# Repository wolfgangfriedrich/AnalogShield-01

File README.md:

# AnalogShield-01
Arduino Schield Pixi Analog I/O 20channel KiCAD design files

Project is hosted at HackADay.io 
https://hackaday.io/project/4397-pixi-analog-shield

Arduino library and sample code are storedin a separate repository 
https://github.com/wolfgangfriedrich/Pixi_demo

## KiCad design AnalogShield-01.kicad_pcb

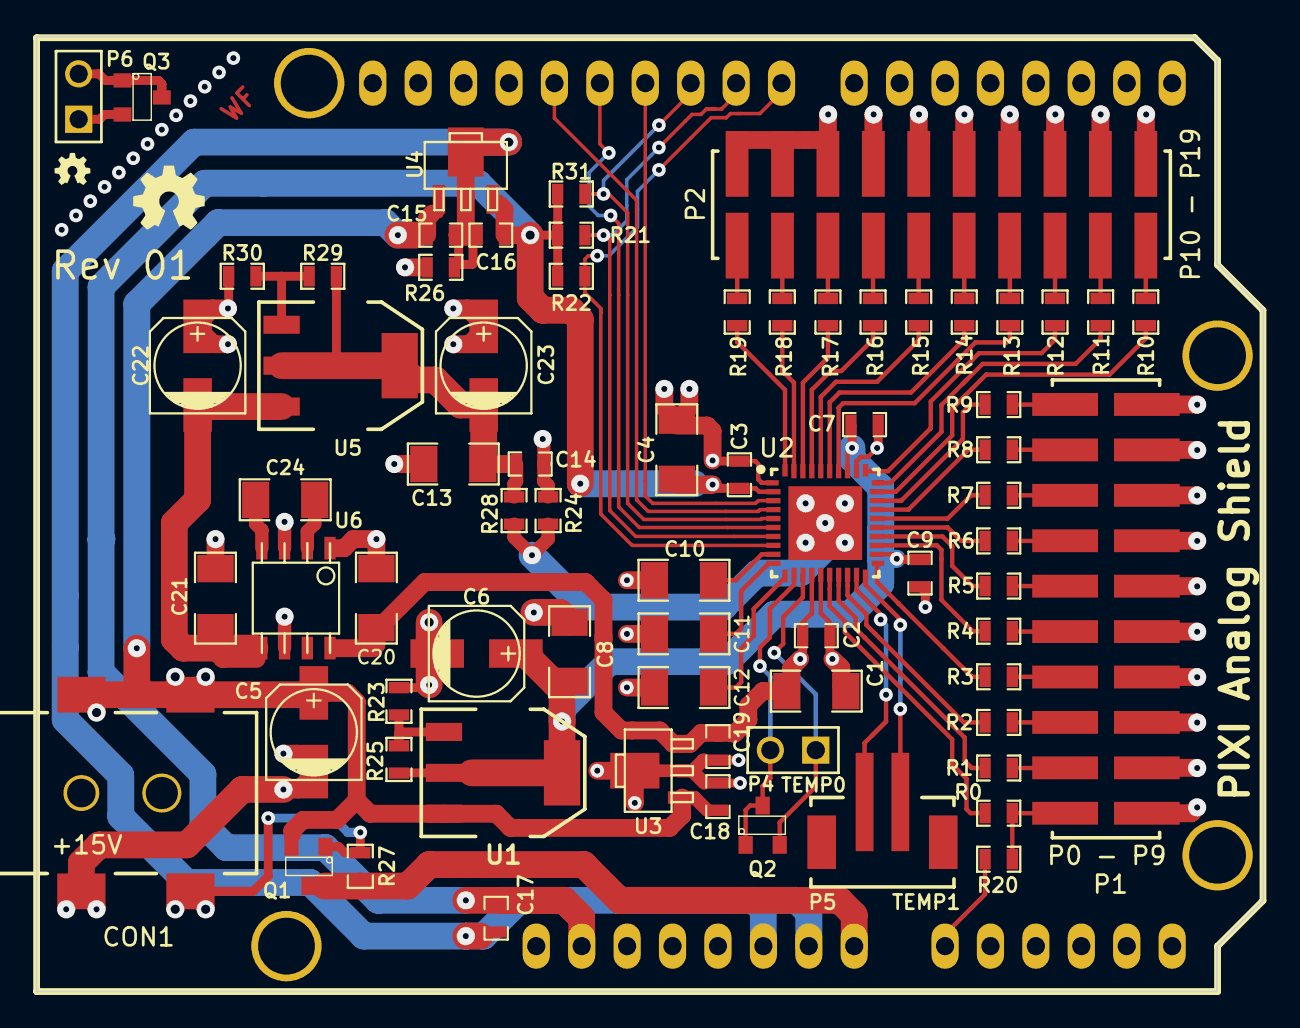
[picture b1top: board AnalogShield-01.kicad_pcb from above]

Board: 2 copper layers, 68.6 x 53.4 mm, 74 parts (0 on the bottom side), 71 nets.

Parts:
C1, C4, C8, C10, C11, C12, C13, C20, C21, C24: 10uF; SM1206
C2, C3, C7, C9, C14, C16, C17, C19: 100nF; SM0603_Capa
C5, C22: 10uF; c_elec_5x5.8
C6, C23: 47uF; c_elec_5x5.8
C15, C18: 330nF; SM0603_Capa
CON1: +15V; ADAM_ADC-028
G1: OSHW-logo_silkscreen-front_4mm
G2: OSHW-logo_silkscreen-front_2mm
P1: P0 - P9; Molex_015912200
P2: P10 - P19; Molex_015912200
P4: TEMP0; PIN_ARRAY_2X1
P5: TEMP1; JST_B2B-PH-SM4-TB
P6: TEMP_EXT; PIN_ARRAY_2X1
Q1: ZXMP6A13FTA; SOT23
Q2, Q3: 3904; SOT23
R0, R1, R2, R3, R4, R5, R6, R7, R8, R9, R10, R11, R12, R13, R14, R15, R16, R17, R18, R19: 10.0R; SM0603_Resistor
R20, R24, R26, R28: 0R; SM0603_Resistor
R21, R22, R27, R31: 4K7; SM0603_Resistor
R23: 1K04; SM0603_Resistor
R25, R29, R30: 120R; SM0603_Resistor
SHIELD1: PIXI Analog Shield; ARDUINO_SHIELD_rev03
U1: LM1117; SOT223
U2: MAX11300GTL+; QFN50P-60X60-41N
U3, U4: 78L05; sot89
U5: LM337; SOT223
U6: LM2663; so-8

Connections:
+5VA: C1.1, C2.1, C19.1, C20.1, U2.14, U3.3, U6.8
-5VA: C21.1, C22.2, U5.3, U6.5
-VAA: C13.2, C14.2, C23.2, R28.1, R29.1, U5.2, U5.Tab
/AD0: R20.1, SHIELD1.AD0
/ADC_EXT_REF: C11.1, U2.10
/ADC_INT_REF: C10.1, U2.9
/AVSSIO: R24.2, R28.2, U2.PAD
/DAC_REF: C12.1, U2.11
/MISO: SHIELD1.12, U2.6
/MOSI: SHIELD1.11, U2.3
/SCK: SHIELD1.13, U2.4
/SW: CON1.3, Q1.G, R27.1
/T0+: P4.2, Q2.1, Q2.3, U2.12
/T0-: P4.1, Q2.2, U2.13
/T1+: P5.2, U2.19
/T1-: P5.1, U2.20
/VDD_IO: C3.1, C4.1, C16.1, C17.1, R21.1, R22.1, R31.1, SHIELD1.VIO, U2.2, U4.3
/V_IN: Q1.D, R27.2, SHIELD1.V_IN
/nCNVT: R22.2, SHIELD1.8, U2.8
/nINT: R21.2, SHIELD1.9, U2.7
/nSS: R31.2, SHIELD1.10, U2.5
AGND: C1.2, C2.2, C5.2, C6.2, C7.2, C8.2, C9.2, C10.2, C11.2, C12.2, C13.1, C14.1, C18.2, C19.2, C20.2, C21.2, C22.1, C23.1, CON1.2, P1.1, P1.3, P1.5, P1.7, P1.9, P1.11, P1.13, P1.15, P1.17, P1.19, P2.1, P2.3, P2.5, P2.7, P2.9, P2.11, P2.13, P2.15, P2.17, P2.19, R23.2, R24.1, R26.1, R30.2, U2.15, U2.32, U3.2, U6.1, U6.3, U6.6
DGND: C3.2, C4.2, C15.2, C16.2, C17.2, R26.2, SHIELD1.GND1, SHIELD1.GND2, SHIELD1.GND3, U2.1, U4.2
unnamed: C24.1, U6.2
unnamed: C24.2, U6.4
unnamed: P1.2, R0.1, R20.2
unnamed: P1.4, R1.1
unnamed: P1.6, R2.1
unnamed: R29.2, R30.1, U5.1
unnamed: P2.4, R11.2
unnamed: P2.8, R13.2
unnamed: P2.12, R15.2
unnamed: R7.2, U2.26
unnamed: P2.10, R14.2
unnamed: P2.14, R16.2
unnamed: P2.18, R18.2
unnamed: P2.2, R10.2
unnamed: P1.16, R7.1
unnamed: P1.10, R4.1
unnamed: P1.12, R5.1
unnamed: P1.14, R6.1
unnamed: P1.18, R8.1
unnamed: P2.16, R17.2
unnamed: P2.20, R19.2
unnamed: R1.2, U2.17
unnamed: P1.8, R3.1
unnamed: R8.2, U2.27
unnamed: R2.2, U2.18
unnamed: P1.20, R9.1
unnamed: P2.6, R12.2
unnamed: P6.2, Q3.1, Q3.3
unnamed: P6.1, Q3.2
unnamed: R11.1, U2.30
unnamed: R19.1, U2.40
unnamed: R3.2, U2.21
unnamed: R12.1, U2.31
unnamed: R4.2, U2.23
unnamed: R5.2, U2.24
unnamed: R13.1, U2.34
unnamed: R6.2, U2.25
unnamed: R14.1, U2.35
unnamed: R0.2, U2.16
unnamed: R10.1, U2.29
unnamed: R15.1, U2.36
unnamed: R16.1, U2.37
unnamed: R9.2, U2.28
unnamed: R17.1, U2.38
unnamed: R18.1, U2.39
unnamed: R23.1, R25.2, U1.1
VAA: C6.1, C7.1, C8.1, C9.1, R25.1, U1.2, U1.Tab, U2.22, U2.33
VCC: C5.1, C15.1, C18.1, CON1.1, Q1.S, U1.3, U3.1, U4.1

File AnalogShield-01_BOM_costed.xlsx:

Value | Qty | Designator | Footprint | Description | Mfr | Mfr PN | Notes | Fitted | Price for 1K | per board |  | Price for Qty 5 | per board | pads
100nF | 8 | C2 C3 C7 C9 C14 C16 C17 C19 | SM0603_Capa | CAP CER 0.1UF 25V 10% X7R 0603 |  |  |  |  | 6.0000000000000001E-3 | 4.8000000000000001E-2 |  | 0.03 | 0.24 | 2 | 16
330nF | 2 | C15 C18 | SM0603_Capa | CAP CER 0.33UF 25V 10% X7R 0603 |  |  |  |  | 6.0000000000000001E-3 | 1.2E-2 |  | 0.03 | 0.06 | 2 | 4
10uF | 1 | C5 | c_elec_5x5.8 | CAP ALUM 10UF 25V 20% 5mm x 5.8mm | Panasonic | EEE-HB1E100AR |  |  | 0.112 | 0.112 |  | 0.62 | 0.62 | 2 | 2
 | 1 | C22 | c_elec_5x5.8 | CAP ALUM 10UF 25V 20% 5mm x 5.8mm | Panasonic | EEE-HB1E100AR |  | DNP |  |  |  |  |  | 2 | 2
10uF | 10 | C1 C4 C8 C10 C11 C12 C13 C20 C21 C24 | SM1206 | CAP CER 10UF 16V 10% X7R 1206 |  |  |  |  | 7.0999999999999994E-2 | 0.71 |  | 0.34 | 3.4000000000000004 | 2 | 20
47uF | 2 | C6 C23 | c_elec_5x5.8 | CAP ALUM 47UF 16V 20% 5mm x 5.8mm | Panasonic | EEE-FPC470UAR | ESR < 0.5 Ohm |  | 0.153 | 0.30599999999999999 |  | 0.73 | 1.46 | 2 | 4
+15V | 1 | CON1 | ADAM_ADC-028 | Connector Barrel Jack 2.1mm SMT | Adam Tech | ADC-028-01 | Sparkfun PRT-12748 |  | 1.2 | 1.2 |  | 1.5 | 1.5 | 4 | 4
TEMP1 | 1 | P5 | JST_B2B-PH-SM4-TB | CONN HEADER PH TOP 2POS 2MM SMD | JST | B2B-PH-SM4-TB |  |  | 0.28999999999999998 | 0.28999999999999998 |  | 0.59 | 0.59 | 4 | 4
P0 - P9, P10 - P19 | 2 | P1 | Molex_015912200 | CONN HEADER 20POS DL UNSHRD SMD | Molex | 15912200 |  |  | 0.99 | 1.98 |  | 1.77 | 3.54 | 20 | 40
TEMP0, TEMP_EXT | 2 | P4 | PIN_ARRAY_2X1 | CONN HEADER .100" SNGL STR 2POS | Sullins | PRPC002SAAN-RC |  | DNP |  |  |  |  |  |  | 0
3904 | 2 | Q2 Q3 | SOT23 | TRANS NPN 40V 200MA SOT-23 | NXP | MMBT3904 |  |  | 2.4E-2 | 4.8000000000000001E-2 |  | 0.12 | 0.24 | 3 | 6
ZXMP6A13FTA | 1 | Q1 | SOT23 | MOSFET P-CH 60V 900MA SOT23-3 | Diodes Inc. | ZXMP6A13FTA |  |  | 0.26400000000000001 | 0.26400000000000001 |  | 0.77 | 0.77 | 3 | 3
0R | 3 | R20 R26 R28 | SM0603_Resistor | RES 0.0 OHM 1A JUMP 0603 SMD |  |  |  |  | 3.0000000000000001E-3 | 9.0000000000000011E-3 |  | 0.02 | 0.06 | 2 | 6
0R | 1 | R24 | SM0603_Resistor | RES 0.0 OHM 1A JUMP 0603 SMD |  |  |  | DNP |  |  |  |  |  | 2 | 2
10.0R | 20 | R0 R1 R2 R3 R4 R5 R6 R7 R8 R9 R10 R11 R12 R13 R14 R15 R16 R17 R18 R19 | SM0603_Resistor | RES 10 OHM 1/10W 1% 0603 |  |  |  |  | 3.0000000000000001E-3 | 0.06 |  | 0.02 | 0.4 | 2 | 40
120R | 3 | R25 R29 R30 | SM0603_Resistor | RES 120 OHM 1/10W 1% 0603 |  |  |  |  | 3.0000000000000001E-3 | 9.0000000000000011E-3 |  | 0.02 | 0.06 | 2 | 6
1K04 | 1 | R23 | SM0603_Resistor | RES 1K04 OHM 1/10W 1% 0603 |  |  |  |  | 3.0000000000000001E-3 | 3.0000000000000001E-3 |  | 0.02 | 0.02 | 2 | 2
4K7 | 4 | R21 R22 R27 R31 | SM0603_Resistor | RES 4.7K OHM 1/10W 5% 0603 SMD |  |  |  |  | 3.0000000000000001E-3 | 1.2E-2 |  | 0.02 | 0.08 | 2 | 8
PIXI Analog Shield | 1 | SHIELD1 | ARDUINO_SHIELD_rev03 | CONN SET ARDUINO SHIELD | Sparkfun | PRT-11417 |  |  | 1.2 | 1.2 |  | 1.5 | 1.5 |  | 0
MAX11300GTL+ | 1 | U2 | QFN50P-60X60-41N | IC 20-PORT ADC DAC SWITCH GPIO TQFN-48 | Maxim | MAX11300GTL+ |  |  | 9.0399999999999991 | 9.0399999999999991 |  | 11.38 | 11.38 | 41 | 41
LM2663 | 1 | U6 | so-8 | IC REG INVERTER SW CAP 0.2A SOIC-8 | TI | LM2663M/NOPB |  |  | 1.17 | 1.17 |  | 2.9 | 2.9 | 8 | 8
LM1117 | 1 | U1 | SOT223 | IC REG LDO ADJ 0.8A SOT223 | ST Micro | LD1117STR |  |  | 0.18 | 0.18 |  | 0.62 | 0.62 | 4 | 4
LM337 | 1 | U5 | SOT223 | IC REG LDO NEG ADJ 1A SOT223 | TI | LM337IMP/NOPB |  | DNP | 0 | 0 |  | 0 | 0 | 4 | 4
78L05 | 1 | U3 | sot89 | IC REG LDO 5V 0.1A SOT89-3 | Fairchild | MC78L05ACH |  |  | 0.16400000000000001 | 0.16400000000000001 |  | 0.59 | 0.59 | 4 | 4
78L05 | 1 | U4 | sot89 | IC REG LDO 5V 0.1A SOT89-3 | Fairchild | MC78L05ACH |  | DNP |  | 0 |  |  | 0 | 4 | 4
 | 1 | PCB |  |  |  |  |  |  | 3.59 | 3.59 |  | 4 | 4
 |  |  |  |  |  |  |  |  | Total | 20.407 |  |  | 34.03 |  | 234

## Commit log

2015-12-27 :lollipop: Added .gitattributes & .gitignore files
2015-12-27 Arduino Schield Pixi Analog I/O 20 channel KiCAD design files
    Rev 01
